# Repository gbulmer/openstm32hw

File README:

openstm32hw README

The aim is to provide Open Source hardware designs for STM32.

This repository grew from a discussion thread on LeafLabs Maple forum:
http://forums.leaflabs.com/topic.php?id=1303

It was initially triggered by ala42 who had released a first cut at libmaple for STM32F4:
http://forums.leaflabs.com/topic.php?id=1268&page=2#post-7828

and siy's hardware design:
http://forums.leaflabs.com/topic.php?id=1303&page=2&replies=46#post-7882

Subdirs:

	MM4 - Leaf Labs Maple Mini clone for 64 pin F1/L1/F4 processors
		in 0.8" width and 2 layers.

	Mini64 - STM32 development board for OpenSTM32
		 Features:
		 - Small (52x38.4mm) breadboard compatible design.
		 - Support for STM32F103/F2xx/F4xx in 64-pin packages.
		 - Uses Eagle 5.1

	Mini48 - Reworked version of Maple Mini suitable for DIY PCB production
		and on-board RTC crystal. Uses Eagle 5.1

	Mini48U - Ultimate version of Mini48. Still suitable for DIY PCB production
		but smaller parts (0402) and optimized layout allowed make it in the
		format of original Maple Mini with 0.6" pin header rows pitch.
		Uses Eagle 5.1

	Mini48SE - This version is very similar to Maple Mini, but it does not 
		preserve its pinout. It also heavily utilizes second side to 
		achieve maximal possible density. As a consequence this version 
		is probably smallest STM32F103Cxx board - it has 0.5" pitch 
		and size is only 50.5x15mm. At the same time board uses no 
		extremely small components - all resistors and capacitors 
		are 0603 (one even 0805), LED - 1206, LDO - 1117.
		Uses Eagle 6.3.0
		The design is tested.

	Mini64SE - Different approach to boards based on MCU in LQFP64 package. 
		It has DIP48 format with 0.8" pitch. The design follows same 
		approach as Mini48SE and utilizes both sides. Separate 
		versions of design for F1 and F2/F4 series are provided. 
		Version for F2/F4 uses different ESD protection and lacks 
		external disconnect cirquitry. These changes are necessary 
		to enable F2/F4 chips work properly in all supported USB modes
		(Device/OTG) and with different powering (self powering and 
		bus powering).
		Uses Eagle 6.3.0 
		Design for F1 is tested, design for F4 still is not yet tested.

	Orone-mini - series of boards intended to be more easily 'DIY-able'
		than LeafLabs Maple-mini, and incorporate several improvements.
		The first boards, Orone-mini-S8x have pins 0.2" wider 
		than Maple-mini. They are otherwise software and pin-compatible 
		with Maple-mini (exception is 'av+' which is intended to 
		improve the power supply capability). 
                Not yet tested.

	PiXe-2: 'Stamp' format, 64pin STM32F103 MCU. Eagle 5.1
                Features: 
		- Dual-in-line 0.1" grid
		- 0805 or larger parts -> easier assembly
		- Internal Maple pins available & re-configurable
		- modest 10mil track/space rules DIY-able

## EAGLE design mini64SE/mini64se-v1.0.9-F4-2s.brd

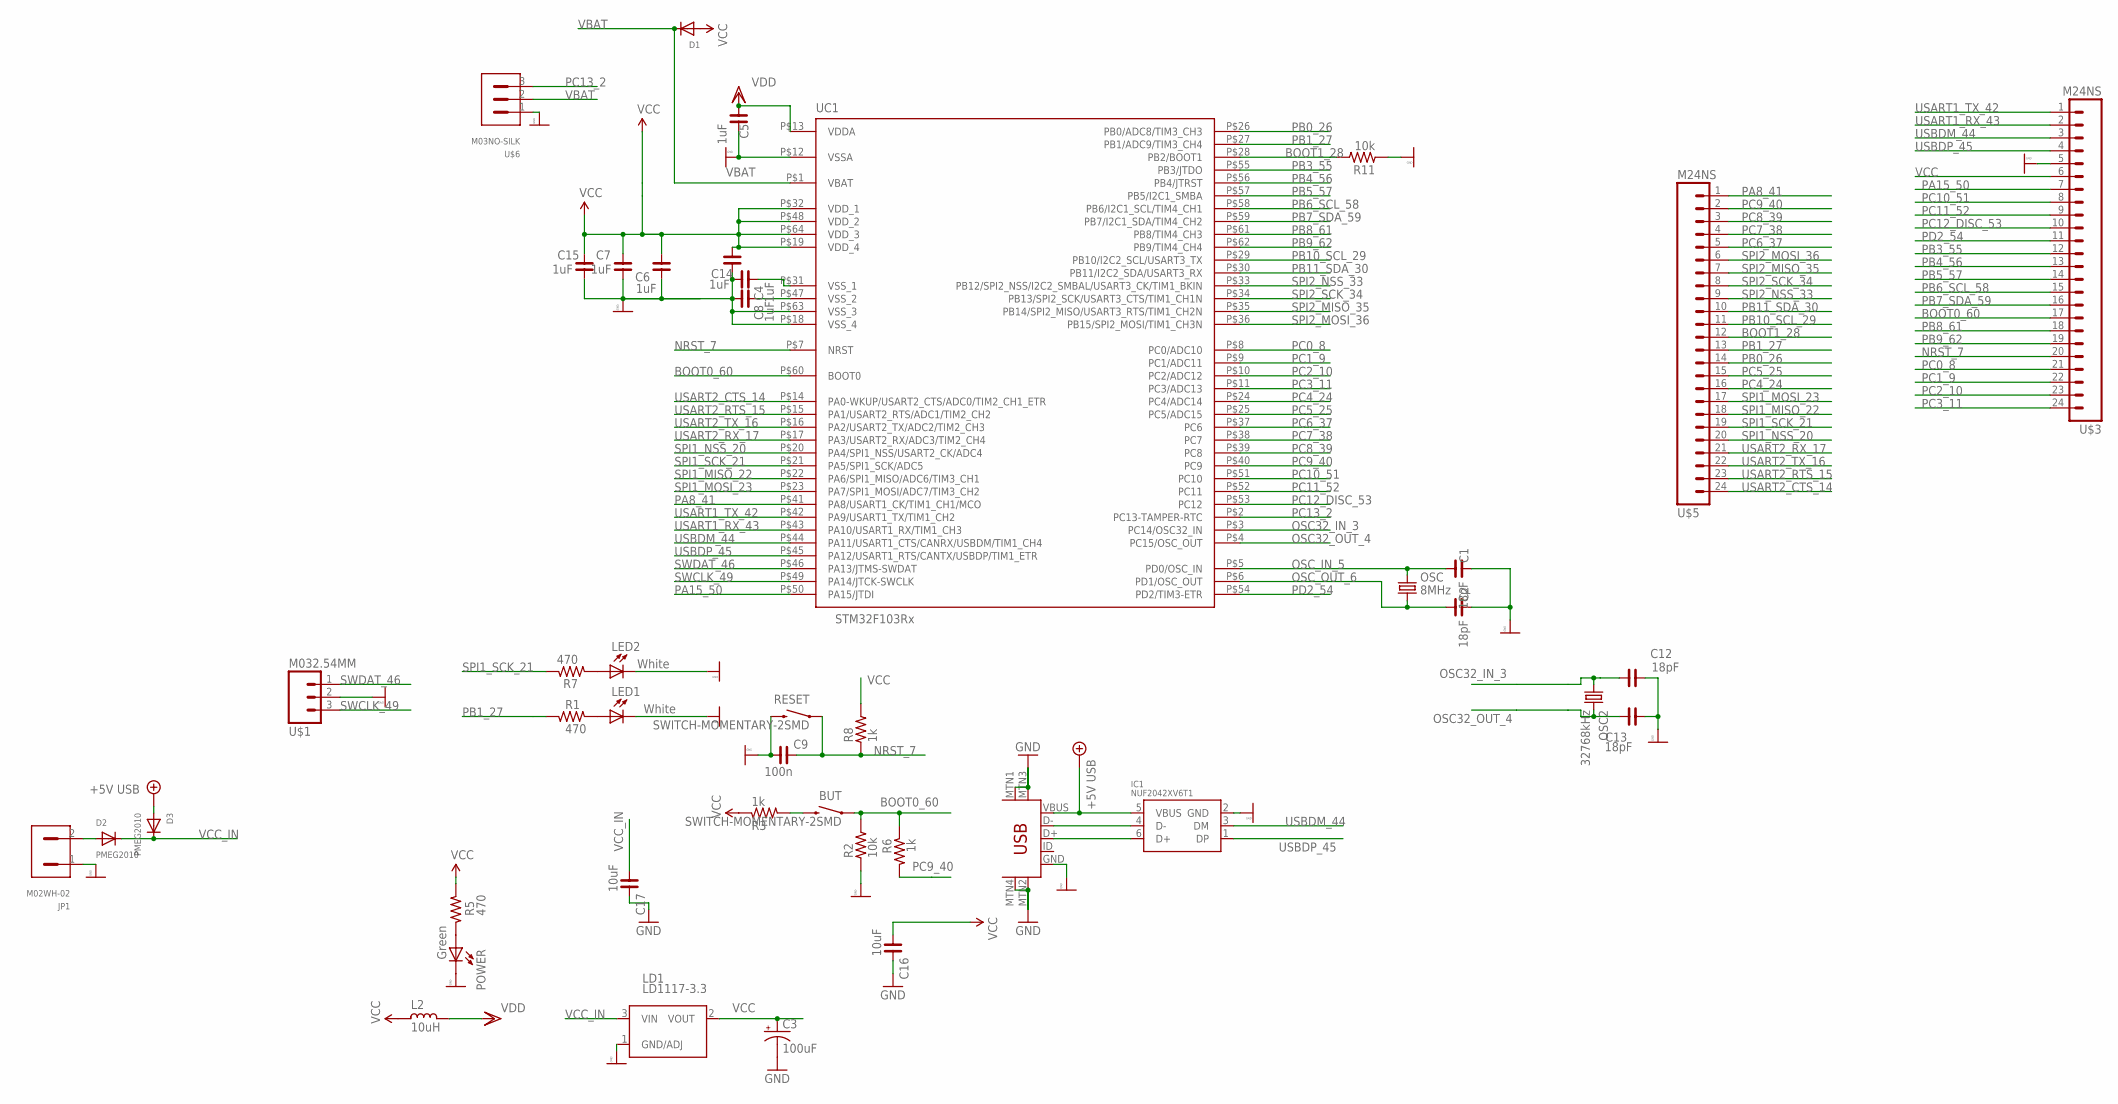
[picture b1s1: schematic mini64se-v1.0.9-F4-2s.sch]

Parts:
BUT: SWITCH-MOMENTARY-2SMD; TACTILE_SWITCH_SMD
C1, C2, C12, C13: 18pF; C0603
C3: 100uF; PANASONIC_C
C4, C5, C6, C7, C8, C14, C15: 1uF; C0603
C9: 100n; C0603
C16, C17: 10uF; C0805
D1: DIODESOD-123; SOD-123
D2, D3: PMEG2010; SOD-123
IC1: NUF2042XV6T1; SOT-563
JP1: M02WH-02; WH-02R
L2: 10uH; PM0603
LD1: LD1117-3.3; SOT223
LED1, LED2: White; CHIPLED_1206
OSC: 8MHz; HC49U-V
OSC2: 32768kHz; TC26H-M
POWER: Green; CHIP-LED0805
R1, R5, R7: 470; R0603
R2, R11: 10k; R0603
R3, R6, R8: 1k; R0603
RESET: SWITCH-MOMENTARY-2SMD; TACTILE_SWITCH_SMD
U$1: M032.54MM; 1X03_NO_SILK
U$3, U$5: M24NS; 1X24_NO_SILK
U$6: M03NO-SILK; 1X03_NO_SILK
UC1: STM32F103Rx; TQFP-10X10-64
USB: USB-MINIB-5PIN; USB-MINIB

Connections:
+5V: D3.A, IC1.5 (VBUS), USB.VBUS
BOOT0_60: BUT.1, R2.2, R6.1, U$3.17 (18), UC1.P$60 (BOOT0)
BOOT1_28: R11.2, U$5.12 (13), UC1.P$28 (PB2/BOOT1)
EXT_PWR: D2.A, JP1.2
GND: C1.1, C2.1, C3.-, C4.2, C5.1, C6.1, C7.1, C8.2, C9.1, C12.1, C13.1, C14.1, C15.1, C16.2, C17.2, IC1.2 (GND), JP1.1, LD1.1 (GND/ADJ), LED1.C, LED2.C, POWER.C, R2.1, R11.1, RESET.3 (2), U$1.2, U$3.5 (6), U$6.1, UC1.P$12 (VSSA), UC1.P$18 (VSS_4), UC1.P$63 (VSS_3), USB.GND, USB.MTN1 (MTN2), USB.MTN2 (MTN3), USB.MTN3 (MTN1), USB.MTN4
unnamed: POWER.A, R5.2
unnamed: BUT.3 (2), R3.2
unnamed: LED2.A, R7.2
unnamed: LED1.A, R1.1
unnamed: C4.1, UC1.P$31 (VSS_1)
unnamed: C8.1, UC1.P$47 (VSS_2)
unnamed: IC1.4 (D-), USB.D-
unnamed: IC1.6 (D+), USB.D+
NRST_7: C9.2, R8.1, RESET.1, U$3.20 (21), UC1.P$7 (NRST)
OSC32_IN_3: C12.2, OSC2.1, UC1.P$3 (PC14/OSC32_IN)
OSC32_OUT_4: C13.2, OSC2.2, UC1.P$4 (PC15/OSC_OUT)
OSC_IN_5: C1.2, OSC.2, UC1.P$5 (PD0/OSC_IN)
OSC_OUT_6: C2.2, OSC.1, UC1.P$6 (PD1/OSC_OUT)
PA8_41: U$5.1 (2), UC1.P$41 (PA8/USART1_CK/TIM1_CH1/MCO)
PA15_50: U$3.7 (8), UC1.P$50 (PA15/JTDI)
PB0_26: U$5.14 (15), UC1.P$26 (PB0/ADC8/TIM3_CH3)
PB1_27: R1.2, U$5.13 (14), UC1.P$27 (PB1/ADC9/TIM3_CH4)
PB3_55: U$3.12 (13), UC1.P$55 (PB3/JTDO)
PB4_56: U$3.13 (14), UC1.P$56 (PB4/JTRST)
PB5_57: U$3.14 (15), UC1.P$57 (PB5/I2C1_SMBA)
PB6_SCL_58: U$3.15 (16), UC1.P$58 (PB6/I2C1_SCL/TIM4_CH1)
PB7_SDA_59: U$3.16 (17), UC1.P$59 (PB7/I2C1_SDA/TIM4_CH2)
PB8_61: U$3.18 (19), UC1.P$61 (PB8/TIM4_CH3)
PB9_62: U$3.19 (20), UC1.P$62 (PB9/TIM4_CH4)
PB10_SCL_29: U$5.11 (12), UC1.P$29 (PB10/I2C2_SCL/USART3_TX)
PB11_SDA_30: U$5.10 (11), UC1.P$30 (PB11/I2C2_SDA/USART3_RX)
PC0_8: U$3.21 (22), UC1.P$8 (PC0/ADC10)
PC1_9: U$3.22 (23), UC1.P$9 (PC1/ADC11)
PC2_10: U$3.23 (24), UC1.P$10 (PC2/ADC12)
PC3_11: U$3.24 (25), UC1.P$11 (PC3/ADC13)
PC4_24: U$5.16 (17), UC1.P$24 (PC4/ADC14)
PC5_25: U$5.15 (16), UC1.P$25 (PC5/ADC15)
PC6_37: U$5.5 (6), UC1.P$37 (PC6)
PC7_38: U$5.4 (5), UC1.P$38 (PC7)
PC8_39: U$5.3 (4), UC1.P$39 (PC8)
PC9_40: R6.2, U$5.2 (3), UC1.P$40 (PC9)
PC10_51: U$3.8 (9), UC1.P$51 (PC10)
PC11_52: U$3.9 (10), UC1.P$52 (PC11)
PC12_DISC_53: U$3.10 (11), UC1.P$53 (PC12)
PC13_2: U$6.3, UC1.P$2 (PC13-TAMPER-RTC)
PD2_54: U$3.11 (12), UC1.P$54 (PD2/TIM3-ETR)
SPI1_MISO_22: U$5.18 (19), UC1.P$22 (PA6/SPI1_MISO/ADC6/TIM3_CH1)
SPI1_MOSI_23: U$5.17 (18), UC1.P$23 (PA7/SPI1_MOSI/ADC7/TIM3_CH2)
SPI1_NSS_20: U$5.20 (21), UC1.P$20 (PA4/SPI1_NSS/USART2_CK/ADC4)
SPI1_SCK_21: R7.1, U$5.19 (20), UC1.P$21 (PA5/SPI1_SCK/ADC5)
SPI2_MISO_35: U$5.7 (8), UC1.P$35 (PB14/SPI2_MISO/USART3_RTS/TIM1_CH2N)
SPI2_MOSI_36: U$5.6 (7), UC1.P$36 (PB15/SPI2_MOSI/TIM1_CH3N)
SPI2_NSS_33: U$5.9 (10), UC1.P$33 (PB12/SPI2_NSS/I2C2_SMBAL/USART3_CK/TIM1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)
SPI2_SCK_34: U$5.8 (9), UC1.P$34 (PB13/SPI2_SCK/USART3_CTS/TIM1_CH1N)
SWCLK_49: U$1.3, UC1.P$49 (PA14/JTCK-SWCLK)
SWDAT_46: U$1.1, UC1.P$46 (PA13/JTMS-SWDAT)
USART1_RX_43: U$3.2 (3), UC1.P$43 (PA10/USART1_RX/TIM1_CH3)
USART1_TX_42: U$3.1 (2), UC1.P$42 (PA9/USART1_TX/TIM1_CH2)
USART2_CTS_14: U$5.24 (25), UC1.P$14 (PA0-WKUP/USART2_CTS/ADC0/TIM2_CH1_ETR)
USART2_RTS_15: U$5.23 (24), UC1.P$15 (PA1/USART2_RTS/ADC1/TIM2_CH2)
USART2_RX_17: U$5.21 (22), UC1.P$17 (PA3/USART2_RX/ADC3/TIM2_CH4)
USART2_TX_16: U$5.22 (23), UC1.P$16 (PA2/USART2_TX/ADC2/TIM2_CH3)
USBDM_44: IC1.3 (DM), U$3.3 (4), UC1.P$44 (PA11/USART1_CTS/CANRX/USBDM/TIM1_CH4)
USBDP_45: IC1.1 (DP), U$3.4 (5), UC1.P$45 (PA12/USART1_RTS/CANTX/USBDP/TIM1_ETR)
VBAT: D1.C, U$6.2, UC1.P$1 (VBAT)
VCC: C3.+, C6.2, C7.2, C14.2, C15.2, C16.1, D1.A, L2.2, LD1.2 (VOUT), R3.1, R5.1, R8.2, U$3.6 (7), UC1.P$19 (VDD_4), UC1.P$32 (VDD_1), UC1.P$48 (VDD_2), UC1.P$64 (VDD_3)
VCC_IN: C17.1, D2.C, D3.C, LD1.3 (VIN)
VDD: C5.2, L2.1, UC1.P$13 (VDDA)

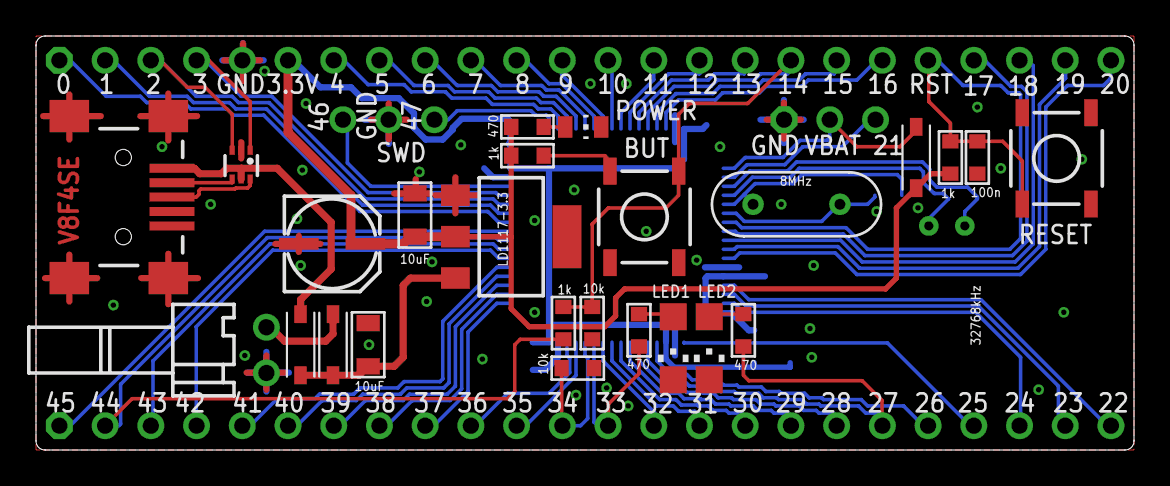
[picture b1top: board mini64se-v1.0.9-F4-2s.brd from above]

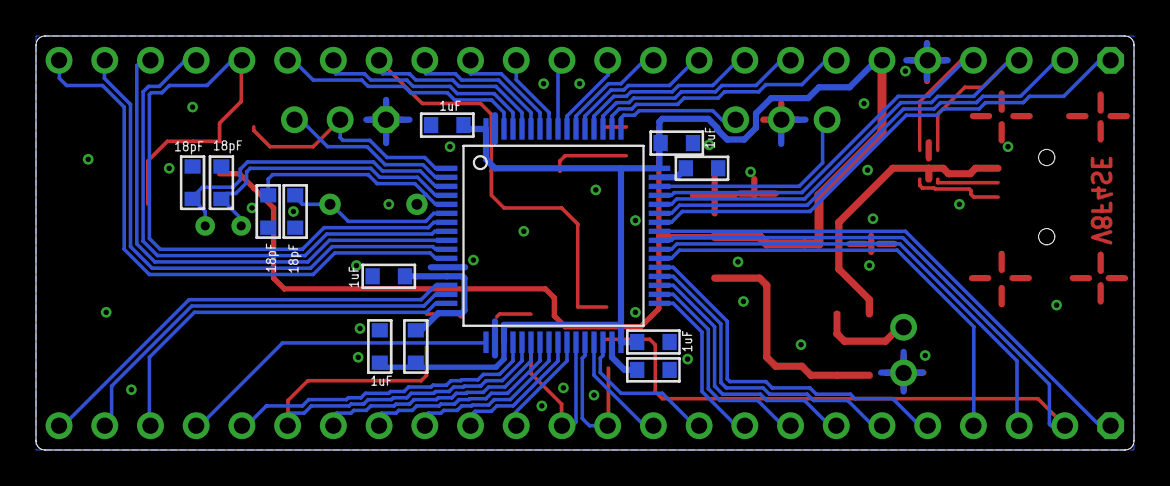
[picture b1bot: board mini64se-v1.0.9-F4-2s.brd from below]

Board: 4 copper layers, 61.0 x 23.0 mm, 43 parts (14 on the bottom side), 68 nets.

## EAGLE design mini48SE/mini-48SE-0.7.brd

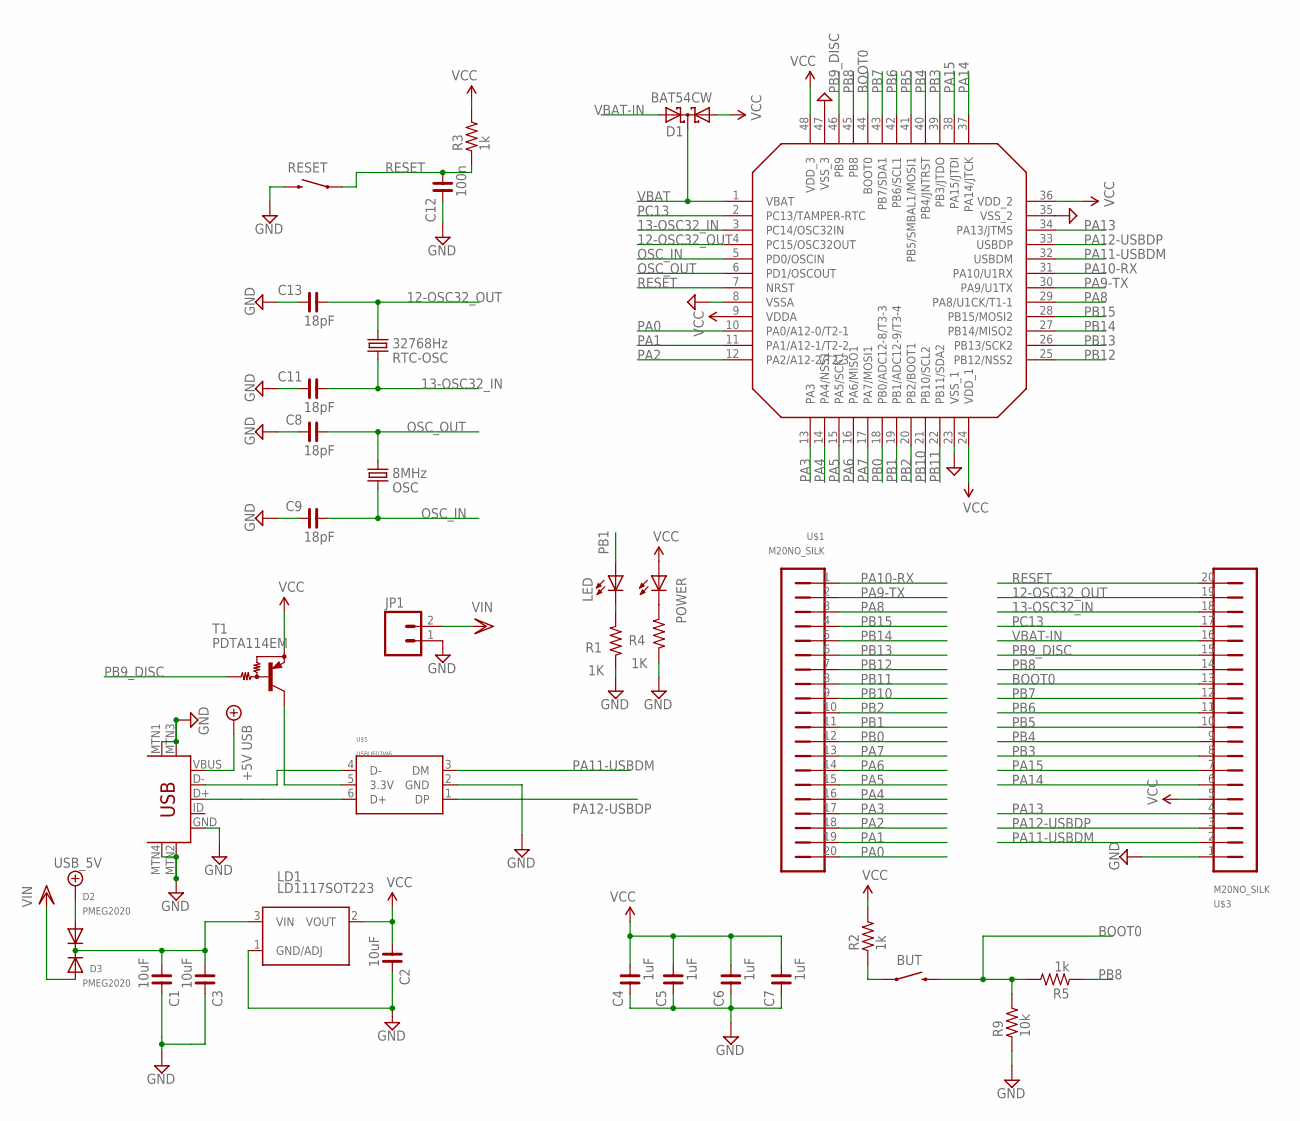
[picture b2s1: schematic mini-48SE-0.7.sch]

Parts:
BUT: SWITCH-MOMENTARY-2TS-1185; TS1185
C1, C3: 10uF; C0603
C2: 10uF; C0805
C4, C5, C6, C7: 1uF; C0603
C8, C9, C11, C13: 18pF; C0603
C12: 100n; C0603
D1: BAT54CW; SOT323R
D2, D3: PMEG2020; SOD-323
JP1: M02-JST-2MM-SMT; JST-2-SMD
LD1: LD1117SOT223; SOT223
LED: LED; CHIPLED_1206
OSC: 8MHz; TC26H-M
POWER: green; CHIP-LED0603
R1, R4: 1K; R0603
R2, R3, R5: 1k; R0603
R9: 10k; R0603
RESET: SWITCH-MOMENTARY-2TS-1185; TS1185
RTC-OSC: 32768Hz; TC26H-M
T1: PDTA114EM; SOT323R
U$1, U$3: M20NO_SILK; 1X20_NO_SILK
U$4: STM32F103_48; LQFP48-7X7
U$5: USBUF02W6; SC70-6
USB: USB-MINIB-5PIN; USB-MINIB

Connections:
12-OSC32_OUT: C13.1, RTC-OSC.1, U$3.19, U$4.4 (PC15/OSC32OUT)
13-OSC32_IN: C11.1, RTC-OSC.2, U$3.18, U$4.3 (PC14/OSC32IN)
+5V/2: D2.A, USB.VBUS
BOOT0: BUT.2, R5.2, R9.2, U$3.13, U$4.44 (BOOT0)
DGND: C1.2, C2.2, C3.2, C4.2, C5.2, C6.2, C7.2, C8.2, C9.2, C11.2, C12.2, C13.2, JP1.1, LD1.1 (GND/ADJ), R1.1, R4.1, R9.1, RESET.2, U$3.1, U$4.8 (VSSA), U$4.23 (VSS_1), U$4.35 (VSS_2), U$4.47 (VSS_3), U$5.2 (GND), USB.GND, USB.MTN1 (MTN2), USB.MTN2 (MTN3), USB.MTN3 (MTN1), USB.MTN4
unnamed: BUT.1, R2.1
unnamed: LED.C, R1.2
unnamed: POWER.C, R4.2
unnamed: C1.1, C3.1, D2.C, D3.C, LD1.3 (VIN)
unnamed: T1.3 (C), U$5.5 (3.3V)
unnamed: U$5.4 (D-), USB.D-
unnamed: U$5.6 (D+), USB.D+
OSC_IN: C9.1, OSC.2, U$4.5 (PD0/OSCIN)
OSC_OUT: C8.1, OSC.1, U$4.6 (PD1/OSCOUT)
PA0: U$1.20, U$4.10 (PA0/A12-0/T2-1)
PA1: U$1.19, U$4.11 (PA1/A12-1/T2-2)
PA2: U$1.18, U$4.12 (PA2/A12-2/T2-3)
PA3: U$1.17, U$4.13 (PA3)
PA4: U$1.16, U$4.14 (PA4/NSS1)
PA5: U$1.15, U$4.15 (PA5/SCK1)
PA6: U$1.14, U$4.16 (PA6/MISO1)
PA7: U$1.13, U$4.17 (PA7/MOSI1)
PA8: U$1.3, U$4.29 (PA8/U1CK/T1-1)
PA9-TX: U$1.2, U$4.30 (PA9/U1TX)
PA10-RX: U$1.1, U$4.31 (PA10/U1RX)
PA11-USBDM: U$3.2, U$4.32 (USBDM), U$5.3 (DM)
PA12-USBDP: U$3.3, U$4.33 (USBDP), U$5.1 (DP)
PA13: U$3.4, U$4.34 (PA13/JTMS)
PA14: U$3.6, U$4.37 (PA14/JTCK)
PA15: U$3.7, U$4.38 (PA15/JTDI)
PB0: U$1.12, U$4.18 (PB0/ADC12-8/T3-3)
PB1: LED.A, U$1.11, U$4.19 (PB1/ADC12-9/T3-4)
PB2: U$1.10, U$4.20 (PB2/BOOT1)
PB3: U$3.8, U$4.39 (PB3/JTDO)
PB4: U$3.9, U$4.40 (PB4/JNTRST)
PB5: U$3.10, U$4.41 (PB5/SMBAL1/MOSI1)
PB6: U$3.11, U$4.42 (PB6/SCL1)
PB7: U$3.12, U$4.43 (PB7/SDA1)
PB8: R5.1, U$3.14, U$4.45 (PB8)
PB9_DISC: T1.1 (B), U$3.15, U$4.46 (PB9)
PB10: U$1.9, U$4.21 (PB10/SCL2)
PB11: U$1.8, U$4.22 (PB11/SDA2)
PB12: U$1.7, U$4.25 (PB12/NSS2)
PB13: U$1.6, U$4.26 (PB13/SCK2)
PB14: U$1.5, U$4.27 (PB14/MISO2)
PB15: U$1.4, U$4.28 (PB15/MOSI2)
PC13: U$3.17, U$4.2 (PC13/TAMPER-RTC)
RESET: C12.1, R3.1, RESET.1, U$3.20, U$4.7 (NRST)
VBAT: D1.3 (CC), U$4.1 (VBAT)
VBAT-IN: D1.2 (A2), U$3.16
VCC: C2.1, C4.1, C5.1, C6.1, C7.1, D1.1 (A1), LD1.2 (VOUT), POWER.A, R2.2, R3.2, T1.2 (E), U$3.5, U$4.9 (VDDA), U$4.24 (VDD_1), U$4.36 (VDD_2), U$4.48 (VDD_3)
VIN: D3.A, JP1.2

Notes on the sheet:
BOOT0

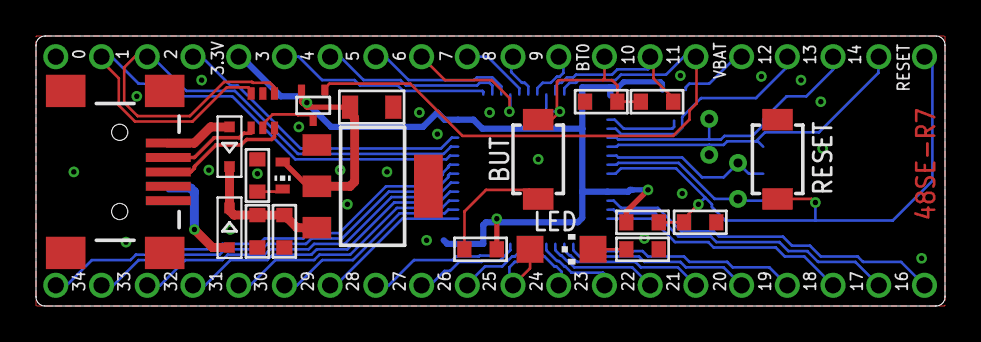
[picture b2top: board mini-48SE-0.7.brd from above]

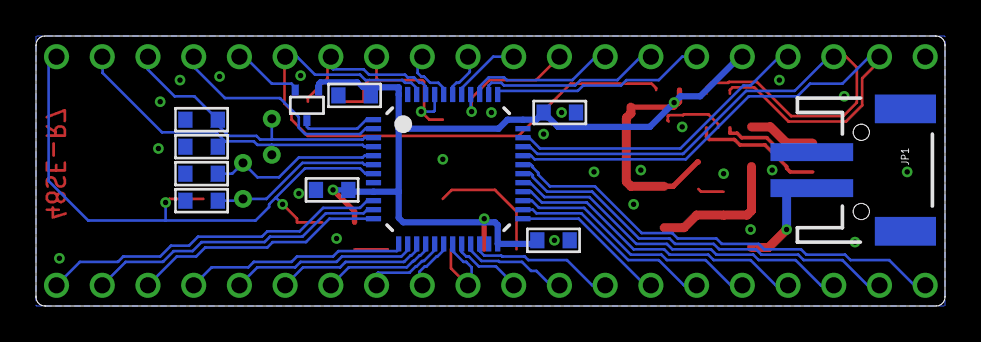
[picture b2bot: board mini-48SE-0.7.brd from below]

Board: 2 copper layers, 50.5 x 15.0 mm, 35 parts (13 on the bottom side), 52 nets.

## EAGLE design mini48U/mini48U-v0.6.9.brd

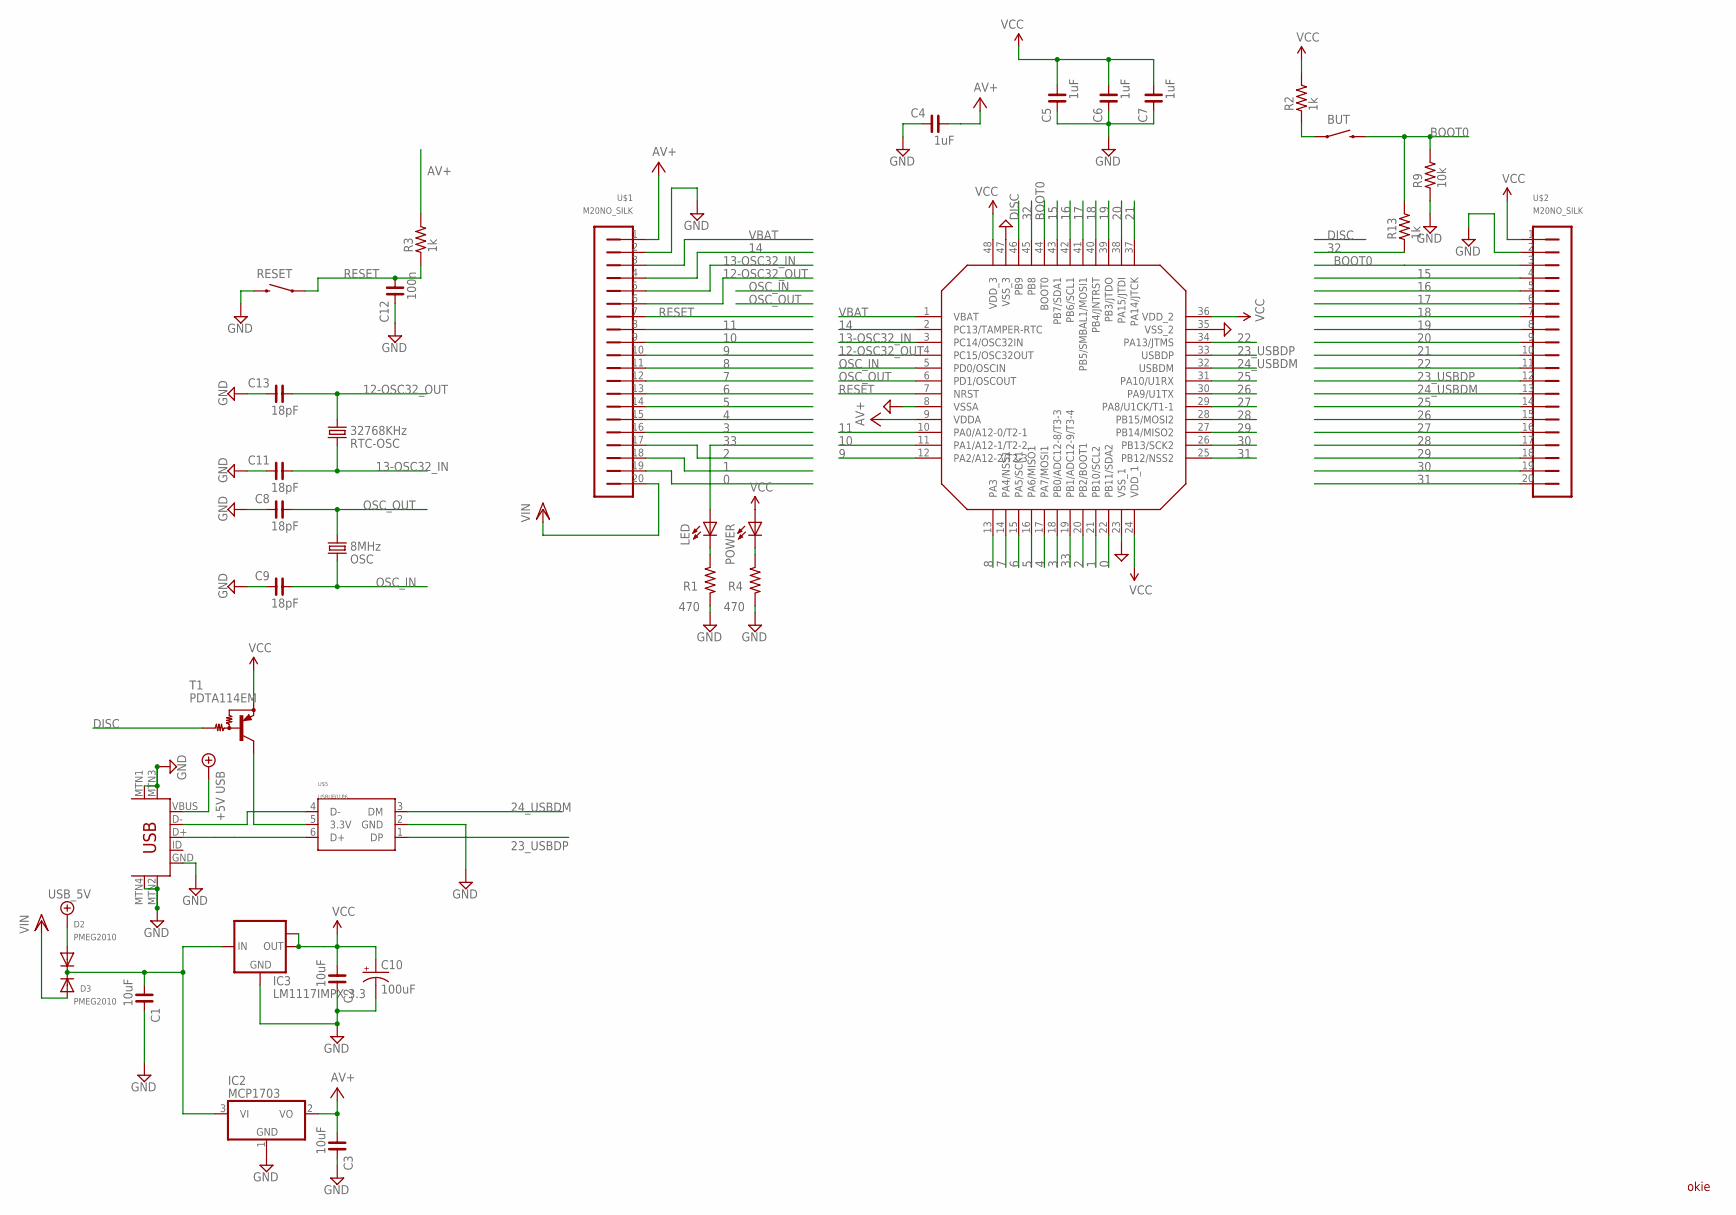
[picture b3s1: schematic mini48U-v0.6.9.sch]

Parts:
BUT: SWITCH-MOMENTARY-2KMR211_NO_GND; KMR211NG
C1, C2, C3: 10uF; C0805
C4, C5, C6, C7: 1uF; C0402
C8, C9, C11, C13: 18pF; C0402
C10: 100uF; EIA3528
C12: 100n; C0402
D2, D3: PMEG2010; SOD-323
IC2: MCP1703; SOT23-3
IC3: LM1117IMPX-3.3; SOT223
LED: LED; KA-3528ASYC
OSC: 8MHz; TC38H
POWER: green; CHIP-LED0603
R1, R4: 470; R0402
R2, R3, R13: 1k; R0402
R9: 10k; R0402
RESET: SWITCH-MOMENTARY-2KMR211_NO_GND; KMR211NG
RTC-OSC: 32768KHz; TC26H
T1: PDTA114EM; SOT-723
U$1, U$2: M20NO_SILK; 1X20_NO_SILK
U$4: STM32F103_48; LQFP48-7X7
U$5: USBUF01P6; SOT-666
USB: USB-MINIB-5PIN; USB-MINIB

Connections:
0: U$1.19, U$4.22 (PB11/SDA2)
1: U$1.18, U$4.21 (PB10/SCL2)
2: U$1.17, U$4.20 (PB2/BOOT1)
3: U$1.16, U$4.18 (PB0/ADC12-8/T3-3)
4: U$1.15, U$4.17 (PA7/MOSI1)
5: U$1.14, U$4.16 (PA6/MISO1)
6: U$1.13, U$4.15 (PA5/SCK1)
7: U$1.12, U$4.14 (PA4/NSS1)
8: U$1.11, U$4.13 (PA3)
9: U$1.10, U$4.12 (PA2/A12-2/T2-3)
10: U$1.9, U$4.11 (PA1/A12-1/T2-2)
11: U$1.8, U$4.10 (PA0/A12-0/T2-1)
12-OSC32_OUT: C13.1, RTC-OSC.1, U$1.6, U$4.4 (PC15/OSC32OUT)
13-OSC32_IN: C11.1, RTC-OSC.2, U$1.5, U$4.3 (PC14/OSC32IN)
14: U$1.4, U$4.2 (PC13/TAMPER-RTC)
15: U$2.4, U$4.43 (PB7/SDA1)
16: U$2.5, U$4.42 (PB6/SCL1)
17: U$2.6, U$4.41 (PB5/SMBAL1/MOSI1)
18: U$2.7, U$4.40 (PB4/JNTRST)
19: U$2.8, U$4.39 (PB3/JTDO)
20: U$2.9, U$4.38 (PA15/JTDI)
21: U$2.10, U$4.37 (PA14/JTCK)
22: U$2.11, U$4.34 (PA13/JTMS)
23_USBDP: U$2.12, U$4.33 (USBDP), U$5.1 (DP)
24_USBDM: U$2.13, U$4.32 (USBDM), U$5.3 (DM)
25: U$2.14, U$4.31 (PA10/U1RX)
26: U$2.15, U$4.30 (PA9/U1TX)
27: U$2.16, U$4.29 (PA8/U1CK/T1-1)
28: U$2.17, U$4.28 (PB15/MOSI2)
29: U$2.18, U$4.27 (PB14/MISO2)
30: U$2.19, U$4.26 (PB13/SCK2)
31: U$2.20, U$4.25 (PB12/NSS2)
32: R13.1, U$4.45 (PB8)
33: LED.A, U$4.19 (PB1/ADC12-9/T3-4)
+5V/2: D2.A, USB.VBUS
AV+: C3.1, C4.1, IC2.2 (VO), R3.2, U$1.1, U$4.9 (VDDA)
BOOT0: BUT.2, R9.2, R13.2, U$2.3, U$4.44 (BOOT0)
DGND: C1.2, C2.2, C3.2, C4.2, C5.2, C6.2, C7.2, C8.2, C9.2, C10.C (-), C11.2, C12.2, C13.2, IC2.1 (GND), IC3.1 (GND), R1.1, R4.1, R9.1, RESET.2, U$1.2, U$2.2, U$4.8 (VSSA), U$4.23 (VSS_1), U$4.35 (VSS_2), U$4.47 (VSS_3), U$5.2 (GND), USB.GND, USB.MTN1 (MTN2), USB.MTN2 (MTN3), USB.MTN3 (MTN1), USB.MTN4
DISC: T1.1 (B), U$4.46 (PB9)
unnamed: BUT.1, R2.1
unnamed: LED.C, R1.2
unnamed: POWER.C, R4.2
unnamed: C1.1, D2.C, D3.C, IC2.3 (VI), IC3.3 (IN)
unnamed: T1.3 (C), U$5.5 (3.3V)
unnamed: U$5.4 (D-), USB.D-
unnamed: U$5.6 (D+), USB.D+
OSC_IN: C9.1, OSC.2, U$4.5 (PD0/OSCIN)
OSC_OUT: C8.1, OSC.1, U$4.6 (PD1/OSCOUT)
RESET: C12.1, R3.1, RESET.1, U$1.7, U$4.7 (NRST)
VBAT: U$1.3, U$4.1 (VBAT)
VCC: C2.1, C5.1, C6.1, C7.1, C10.A (+), IC3.2 (OUT), IC3.TAB (OUT1), POWER.A, R2.2, T1.2 (E), U$2.1, U$4.24 (VDD_1), U$4.36 (VDD_2), U$4.48 (VDD_3)
VIN: D3.A, U$1.20

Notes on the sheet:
okie
BOOT0

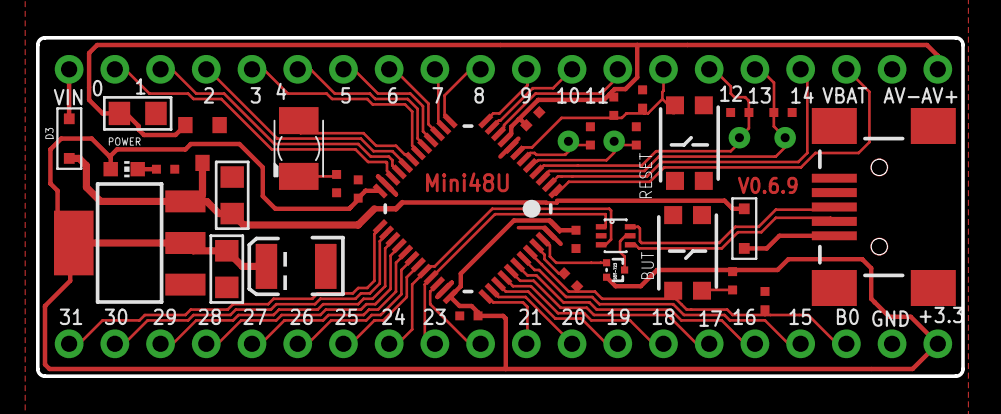
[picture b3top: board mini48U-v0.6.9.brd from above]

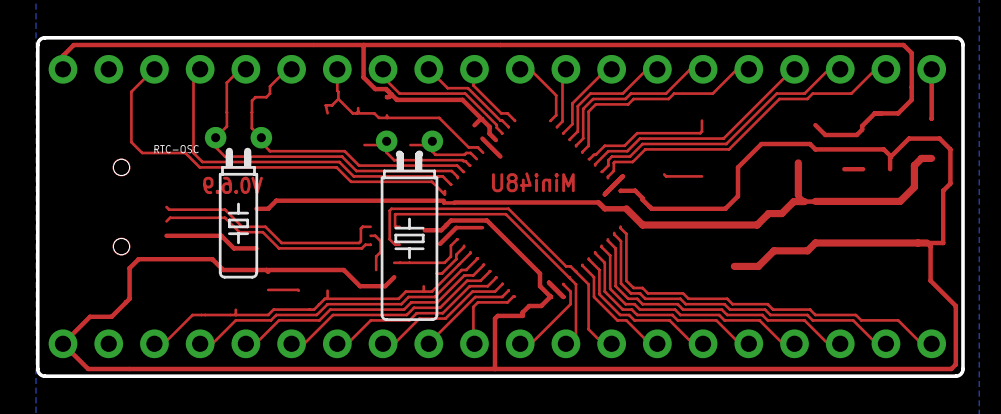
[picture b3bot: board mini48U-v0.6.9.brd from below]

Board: 2 copper layers, 51.4 x 18.8 mm, 35 parts (2 on the bottom side), 52 nets.

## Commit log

2012-01-29 added Mini64 board
2012-01-30 Original r0 variant of MM4 board added
2012-01-31 Updated to give brief summary of the two STM32 boards, thanks to siy for Mini64 and rod for MM4
2012-01-31 Fixed copyright notices, added PDF.
2012-02-05 Added Mini48 design.
2012-02-07 Added version of Eagle on Mini48 and Mini64
2012-02-07 Added piXe-2 - Work-In-Progress - 'Stamp' format, DIL board for 64pin STM32F103
2012-02-16 Added Mini48, minor cleanups
2012-03-18 Added new version of Mini48U
2012-03-21 Corrected tiny spelling mistakes
2013-04-04 Added three new designs.
2013-04-04 Added comments for new designs.
2013-04-04 Updated README.
2013-04-11 Added First version of Orone-mini-S8A, DIY-able Maple-mini-like board.
    First Commit of Orone-mini and Orone-mini-S8A-v0r001, Maple-mini-like STM32F board.
2013-04-11 Updated README to show addition of Orone-mini
2013-04-12 Added USB-Mini-Molex.lbr which contains three different footprints for the Molex socket. Updated README files to reflect untested status.
2013-04-12 Segregated ground plane under ADC signals re-connected to av-. Intent is to provide a less noisy ground plane under ADC input signals.
2013-04-14 Created initial Bill of Materials (BoM) using RS, Farnell & Future (for ESD only). TBD: 100uF capacitor. Modified CAD to hide redundant airwires.
2013-04-15 Added Orone-mini-S8C, modified BoMs for S8A and S8C variants, added markdown to README
2013-04-15 Corrected small error in markdown.
2013-04-15 Tweaked position of User LED (pin 33) and added thru-hole pad for DISC (PB9) putting holes onto 0.1" grid. These give access to the two signals not on pin-headers, though the User LED must not be fit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
2013-04-16 Updated README's describing 'Tweaked' position of User LED pads and DISC 'via' to give access to signals.
2013-04-16 First checkin of Orone-mini-S8D, puts User LED (33) next to pin header, and DISC signal onto a pad. Also changed position of Power-on and User LED.
2013-04-18 Moved BoM files into their own directory, and added costs from RS and Future.
2013-04-18 Updated top-level README.md to explain the Orone-mini-S8D.
2013-04-19 Updated README to reflect changes in design test status for Mini48SE and Mini64SE.
2013-04-23 Small adjustments to PCB.
2013-04-29 Added 8mil/8mil S8H design.
2013-04-29 Added Digikey bom, created by ventosus.
2013-05-05 Added English Headings and deleted lines containing dates from ventosus Digi-Key BoM. Slightly improved wording on original BoM.
2013-05-05 Added Vusb & Vx (regulator) pads. Rerouted ground, analogue ground, MCU top-side copper pour, and USB D+ to reduce noise.
2013-05-05 Updated comments on Schematic to reflect added voltage pads.
2013-05-06 Changed voltage pads (Vusb & Vx) to match other (e.g. S8D) boards. Adjusted ground for better return path. Reduced USB R-pull-up 'stub track' for less signal reflection. Moved LED1 so 3mm LED could b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
2013-05-20 Adjusted USB 'DISC' pad to support 2 x 0.1" header, intended to help STM32F303 boot from USB using built-in bootloader. Increased clearance between STM32F and capacitors, intended to help assembly an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
2013-05-20 Updated formatting for README.md files to show numbered lists correctly.
2013-05-22 Initial release of OSH Park compatible CAM file. Changed from OSHPark's normal CAM file to support User 'top' (Eagle bottom) silk screen Updated Orone-mini-S8H to match Orone-mini-S8E: Adjusted USB '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
2013-05-23 Updated README to indicate that 'succeeded' boards are not likely to be tested.
2013-05-23 Modified silk screen 'USB only' to avoid problems generating reversed text. Changed all _bsilk layer text and lines to bPlace layer; Eagle does better error checks for silk screen overalpping with co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
2014-01-05 Added Orone-mini-S8J-v0r001. USB EMI/ESDi replaced, analogue supply and ground plane reworked.
2014-01-22 fixed two airwires, updated README files
2014-01-23 New S8K: DISC+Ground header moved, and connected USB shield to USB ground
2014-01-23 Updated README documentation for latest S8K variant and Orone-mini overall
